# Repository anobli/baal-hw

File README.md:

# Beal

Beal is a **LoRa valve-control proxy** that retrofits an existing irrigation
controller with remote, wire-free zone control.

## Why

Irrigation controllers are typically wire-only: reaching a new zone, or a
valve far from the controller box, means trenching new low-voltage wiring
across a working field — labor-intensive and disruptive.

Beal solves that wiring problem: clip a **RX** unit onto the existing
controller (no new wiring, no controller replacement) and place **TX** units
directly at the valves; they talk over LoRa, so control reaches valves
without trenching.

## How it works

Two dedicated boards make up one system:

| Board | Role | What it does |
| --- | --- | --- |
| [**Beal-Rx**](Beal-Rx/README.md) | Input | Clips onto the existing controller's zone-output wiring, senses which zone it's energizing, and reports over LoRa. Acts as the LoRa coordinator. |
| [**Beal-TX**](Beal-TX/README.md) | Output | Lives out at the valves, powered by its own battery + solar supply. Drives valve solenoids on command from Beal-Rx. Acts as a LoRa peer. |

```mermaid
flowchart TD
    VC["Existing valve controller<br/>(zone outputs)"] -->|wired, no new cabling| RX["Beal-Rx<br/>LoRa coordinator"]
    RX -->|LoRa P2P, star topology| TX1["Beal-TX #1<br/>LoRa peer"]
    RX -->|LoRa P2P, star topology| TX2["Beal-TX #2<br/>LoRa peer"]
    TX1 -->|wired| V1["Valves — zone A"]
    TX2 -->|wired| V2["Valves — zone B"]
```

The link between Beal-Rx and Beal-TX units is point-to-point LoRa, not
LoRaWAN: a custom, open-source stack with a star topology. Beal-Rx is the
coordinator — it's where commands originate and it's already the central
device by virtue of being wired to the existing controller. Beal-TX units are
peer nodes that take commands from it. LoRaWAN is deliberately avoided for
now — it would require network-server infrastructure disproportionate to
stand up and operate for this product.

## Repository layout

| Folder | What it is |
| --- | --- |
| [`Beal-Rx/`](Beal-Rx/README.md) | Input board: KiCad project, schematics, PCB. |
| [`Beal-TX/`](Beal-TX/README.md) | Output board: KiCad project, schematics, PCB. |
| `Beal-Common/` | Reusable elements shared between boards — currently footprints, with symbol libraries and design blocks planned. |

Schematic PDFs and BOMs are generated automatically on every push via
[`.github/workflows/kicad-schematic-pdf.yml`](.github/workflows/kicad-schematic-pdf.yml).

## What's next: Beal Controller

Both boards share the same LoRa-E5-centric approach, which is also the seed
for a future third board — tentatively **Beal Controller**. It would be a
smart irrigation controller with its own valve outputs and smart features
(weather-driven scheduling, ET0 computation, local web UI), while still able
to control remote valves over LoRa through a Beal-TX unit — replacing the
third-party controller entirely instead of just retrofitting it. This is a
future direction, not yet designed.

## License

Hardware design files are licensed under the
[CERN Open Hardware Licence Version 2 - Strongly Reciprocal](LICENSE).

## Open items

- [ ] Battery chemistry/capacity for the Beal-TX power pack — not yet sized.
- [ ] Enclosure — to do, no design started.
- [ ] Regulatory/certification path for the radio — not started; complicated
      by the use of a custom (non-LoRaWAN) PHY/MAC stack.
- [ ] Unit cost target (below 250 € incl. VAT) — needs re-costing against the
      current RX/TX design.
- [ ] Beal Controller — not designed yet; see above.

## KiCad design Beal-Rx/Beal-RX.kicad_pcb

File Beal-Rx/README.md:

# Beal-Rx — input board

Beal-Rx clips onto an existing irrigation controller's zone-output wiring,
senses which zone it's energizing, and reports that over LoRa to one or more
[Beal-TX](../Beal-TX/README.md) units. It is the LoRa coordinator of a Beal
system — it's where commands originate, and it's already the natural central
device since it's the one wired to the existing controller.

The schematic is split into three sheets: **Inputs**, **Radio**, **Power**.

## Inputs (`io_ext.kicad_sch`)

- 12 sense channels, each isolated from the field wiring by an opto-isolator
  (3× LTV-844S, 4 channels each). This gives galvanic isolation from whatever
  the existing controller puts on its zone outputs, with no current drawn
  from or injected back into the controller.
- Sized against 24VAC zone outputs but tolerant of smaller signals
  (9VAC/9VDC), so the same board can read other controller types without a
  hardware change.
- A 14-position terminal block (`TBL004-508-14BE-2GY`) brings in the 12
  channels plus the shared `INPUT_COM` return.
- A dedicated **STM32C031K6Ux MCU** on this sheet scans all 12 opto outputs
  and reports state changes up to the LoRa-E5 (I2C/UART, plus an interrupt
  line) — the LoRa-E5 doesn't have enough spare GPIOs to read 12 channels
  directly itself, so this small companion MCU owns the input-scanning job.
  It has its own SWD (TC2050) connector for programming/debug.

## Radio (`radio_mcu.kicad_sch`)

- **LoRa-E5 module** (U5, Seeed, STM32WL-based) — the application MCU. It
  owns the LoRa radio, drives the status LED (D3), reads the pairing button
  (SW2, on its own dedicated GPIO), and talks to the Inputs sheet's
  STM32C031 over I2C/UART to learn which zone just turned on.
- Pairing button (SW2) behavior:
  - Short press: pairs this coordinator with a Beal-TX peer (implemented).
  - Double press: maps a specific input channel to a specific output channel
    on a specific Beal-TX (planned, procedure still TBD).
  - Long press: probable factory reset (not decided).
- U.FL/antenna connector (J1) for the 868 MHz antenna.
- USB-C connector (J5) — power input only.
- SWD (Tag-Connect J7) for programming/debugging the LoRa-E5.
- One extension connector (J2, `Conn_02x04_Odd_Even`) reserved for a future
  add-on board (e.g. more sense inputs) — not used by anything today.

## Power (`power.kicad_sch`)

- `TPSM863253` buck power module producing the board's logic-level rail from
  USB 5V. No boost converter or valve driver on this board — Beal-Rx only
  senses, it never drives anything, so it has no need for the 9V drive rail
  that Beal-TX needs.
- Powered from a 5V USB supply (mains-adapter or similar) — it lives next to
  the existing controller, which typically has power available nearby.

## Open items

- [ ] Channel-to-channel mapping procedure (input on Beal-Rx → output on a
      specific Beal-TX) — design not finalized.
- [ ] Long-press button behavior (factory reset) — not decided.
- [ ] Extension connector (J2) use case — reserved, nothing designed against
      it yet.

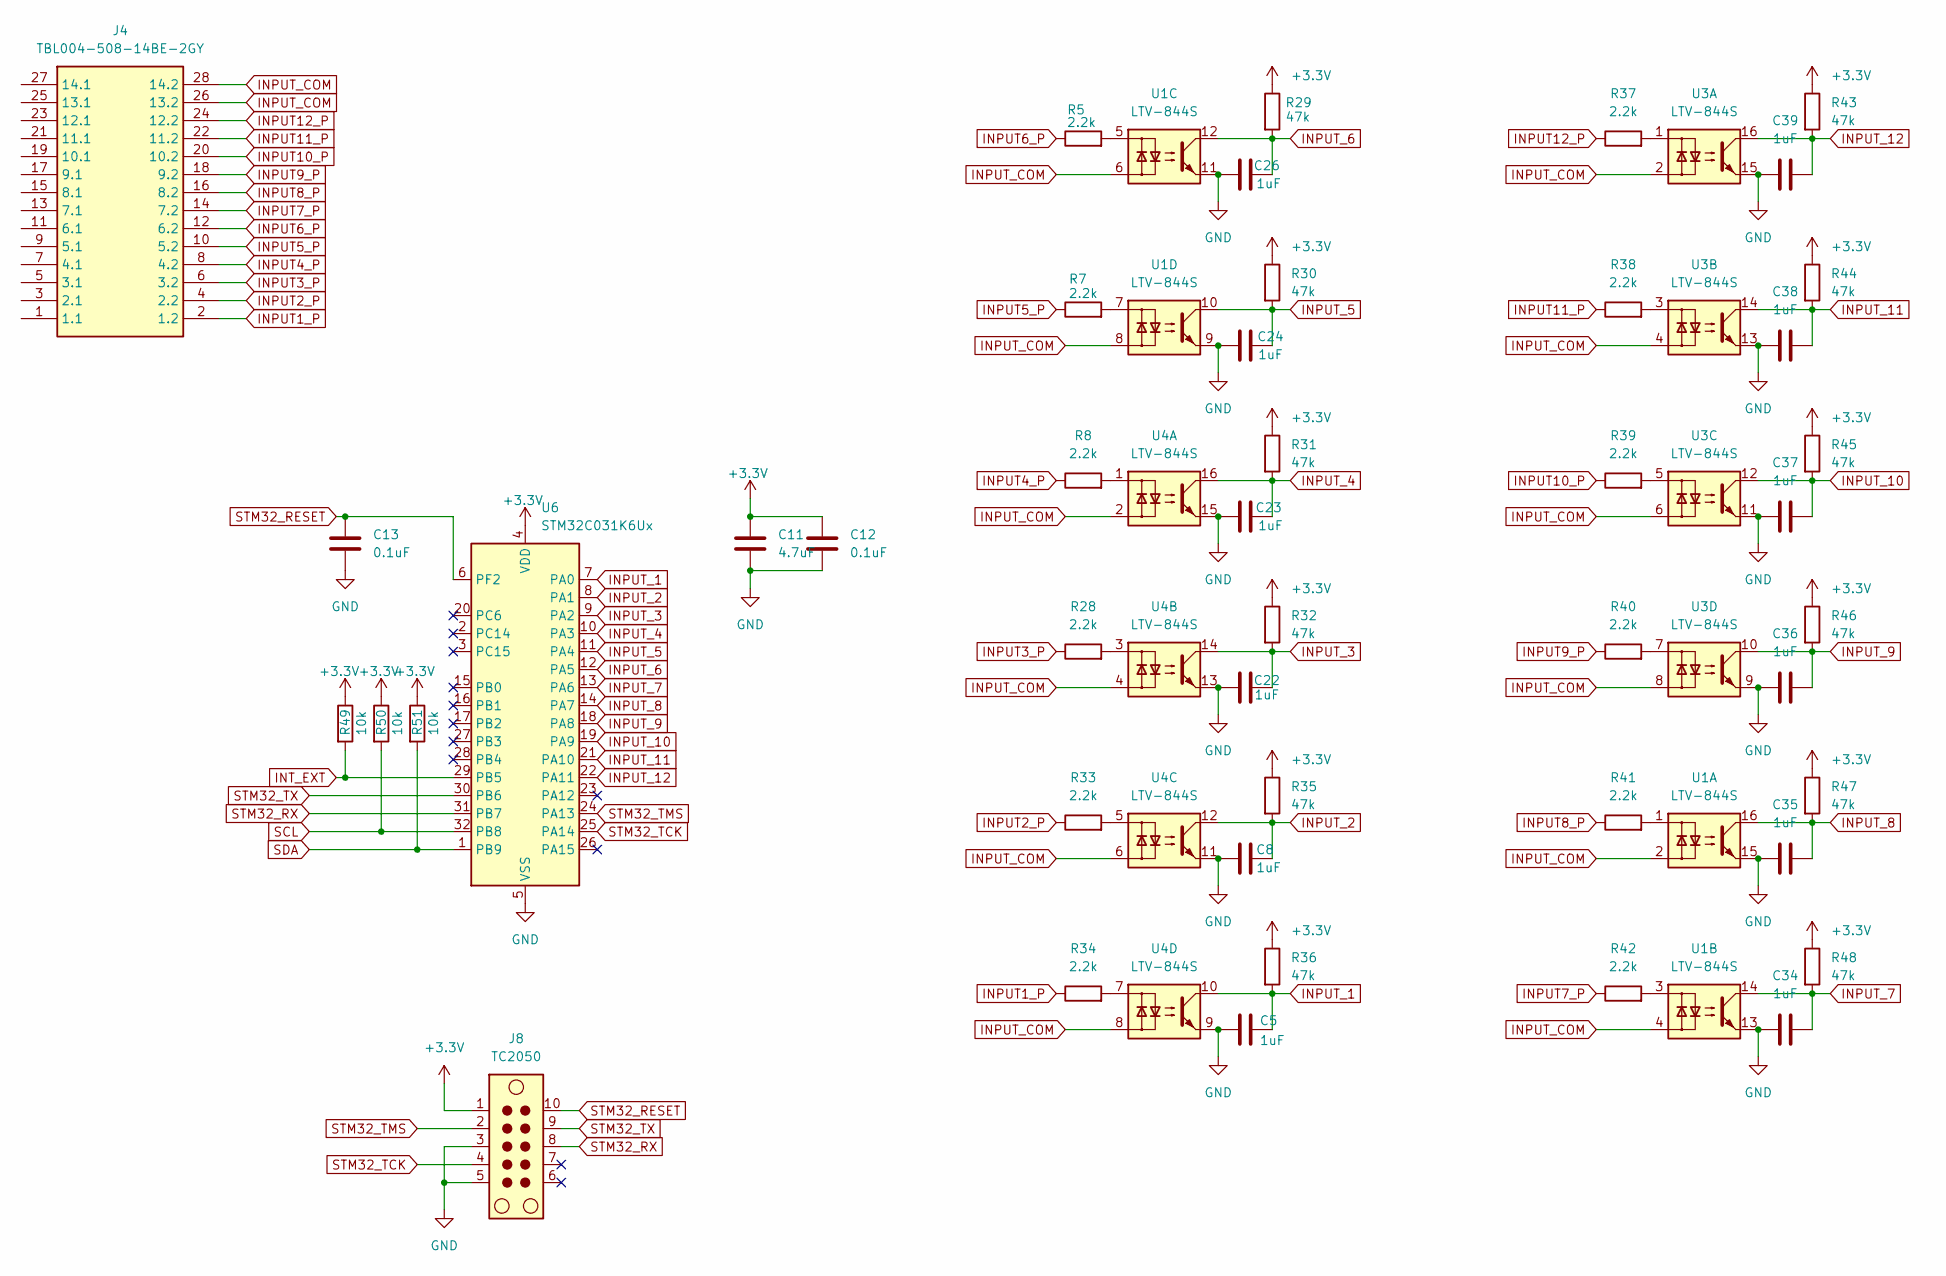
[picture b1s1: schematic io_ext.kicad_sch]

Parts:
C5, C8, C22, C23, C24, C26, C34, C35, C36, C37, C38, C39: 1uF; C_0603_1608Metric; Manufacturer_Part_Number 1uF 16V 0603
C11: 4.7uF; C_0805_2012Metric; MPN 4.7uF 10V 0805
C12, C13: 0.1uF; C_0805_2012Metric; MPN 0.1uF 10V 0805
J4: TBL004-508-14BE-2GY; Mouser Part Number 490-TBL00450814BE2GY
J8: TC2050; Tag-Connect_TC2050-IDC-NL_2x05_P1.27mm_Vertical
R5, R7, R8, R28, R33, R34, R37, R38, R39, R40, R41, R42: 2.2k; R_0402_1005Metric; Manufacturer_Part_Number 2.2K 0402
R29, R30, R31, R32, R35, R36, R43, R44, R45, R46, R47, R48: 47k; R_0402_1005Metric; Manufacturer_Part_Number 47K 0402
R49, R50, R51: 10k; R_0402_1005Metric; MPN 10k 0402
U1, U3, U4: LTV-844S; SMDIP-16_W9.53mm; MPN LTV-844S
U6: STM32C031K6Ux; QFN-32-1EP_5x5mm_P0.5mm_EP3.45x3.45mm; MPN STM32C031K6U6

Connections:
+3.3V: C11.1, C12.1, J8.1, R29.1, R30.1, R31.1, R32.1, R35.1, R36.1, R43.1, R44.1, R45.1, R46.1, R47.1, R48.1, R49.1, R50.1, R51.1, U6.4 (VDD); also elsewhere on the board
GND: C5.1, C8.2, C11.2, C12.2, C13.2, C22.1, C23.1, C24.2, C26.2, C34.1, C35.1, C36.1, C37.1, C38.2, C39.1, J8.3, J8.5, U1.9, U1.11, U1.13, U1.15, U3.9, U3.11, U3.13, U3.15, U4.9, U4.11, U4.13, U4.15, U6.5 (VSS), U6.33 (VSS); also elsewhere on the board
INPUT1_P: J4.2 (1.2), R34.1
INPUT2_P: J4.4 (2.2), R33.1
INPUT3_P: J4.6 (3.2), R28.1
INPUT4_P: J4.8 (4.2), R8.1
INPUT5_P: J4.10 (5.2), R7.1
INPUT6_P: J4.12 (6.2), R5.1
INPUT7_P: J4.14 (7.2), R42.1
INPUT8_P: J4.16 (8.2), R41.1
INPUT9_P: J4.18 (9.2), R40.1
INPUT10_P: J4.20 (10.2), R39.1
INPUT11_P: J4.22 (11.2), R38.1
INPUT12_P: J4.24 (12.2), R37.1
INPUT_1: C5.2, R36.2, U4.10, U6.7 (PA0)
INPUT_2: C8.1, R35.2, U4.12, U6.8 (PA1)
INPUT_3: C22.2, R32.2, U4.14, U6.9 (PA2)
INPUT_4: C23.2, R31.2, U4.16, U6.10 (PA3)
INPUT_5: C24.1, R30.2, U1.10, U6.11 (PA4)
INPUT_6: C26.1, R29.2, U1.12, U6.12 (PA5)
INPUT_7: C34.2, R48.2, U1.14, U6.13 (PA6)
INPUT_8: C35.2, R47.2, U1.16, U6.14 (PA7)
INPUT_9: C36.2, R46.2, U3.10, U6.18 (PA8)
INPUT_10: C37.2, R45.2, U3.12, U6.19 (PA9)
INPUT_11: C38.1, R44.2, U3.14, U6.21 (PA10)
INPUT_12: C39.2, R43.2, U3.16, U6.22 (PA11)
INPUT_COM: J4.26 (13.2), J4.28 (14.2), U1.2, U1.4, U1.6, U1.8, U3.2, U3.4, U3.6, U3.8, U4.2, U4.4, U4.6, U4.8
INT_EXT: R49.2, U6.29 (PB5); also elsewhere on the board
unnamed: R5.2, U1.5
unnamed: R7.2, U1.7
unnamed: R8.2, U4.1
unnamed: R28.2, U4.3
unnamed: R33.2, U4.5
unnamed: R34.2, U4.7
unnamed: R37.2, U3.1
unnamed: R38.2, U3.3
unnamed: R39.2, U3.5
unnamed: R40.2, U3.7
unnamed: R41.2, U1.1
unnamed: R42.2, U1.3
SCL: R50.2, U6.32 (PB8); also elsewhere on the board
SDA: R51.2, U6.1 (PB9); also elsewhere on the board
STM32_RESET: C13.1, J8.10, U6.6 (PF2)
STM32_RX: J8.8, U6.31 (PB7)
STM32_TCK: J8.4, U6.25 (PA14)
STM32_TMS: J8.2, U6.24 (PA13)
STM32_TX: J8.9, U6.30 (PB6)

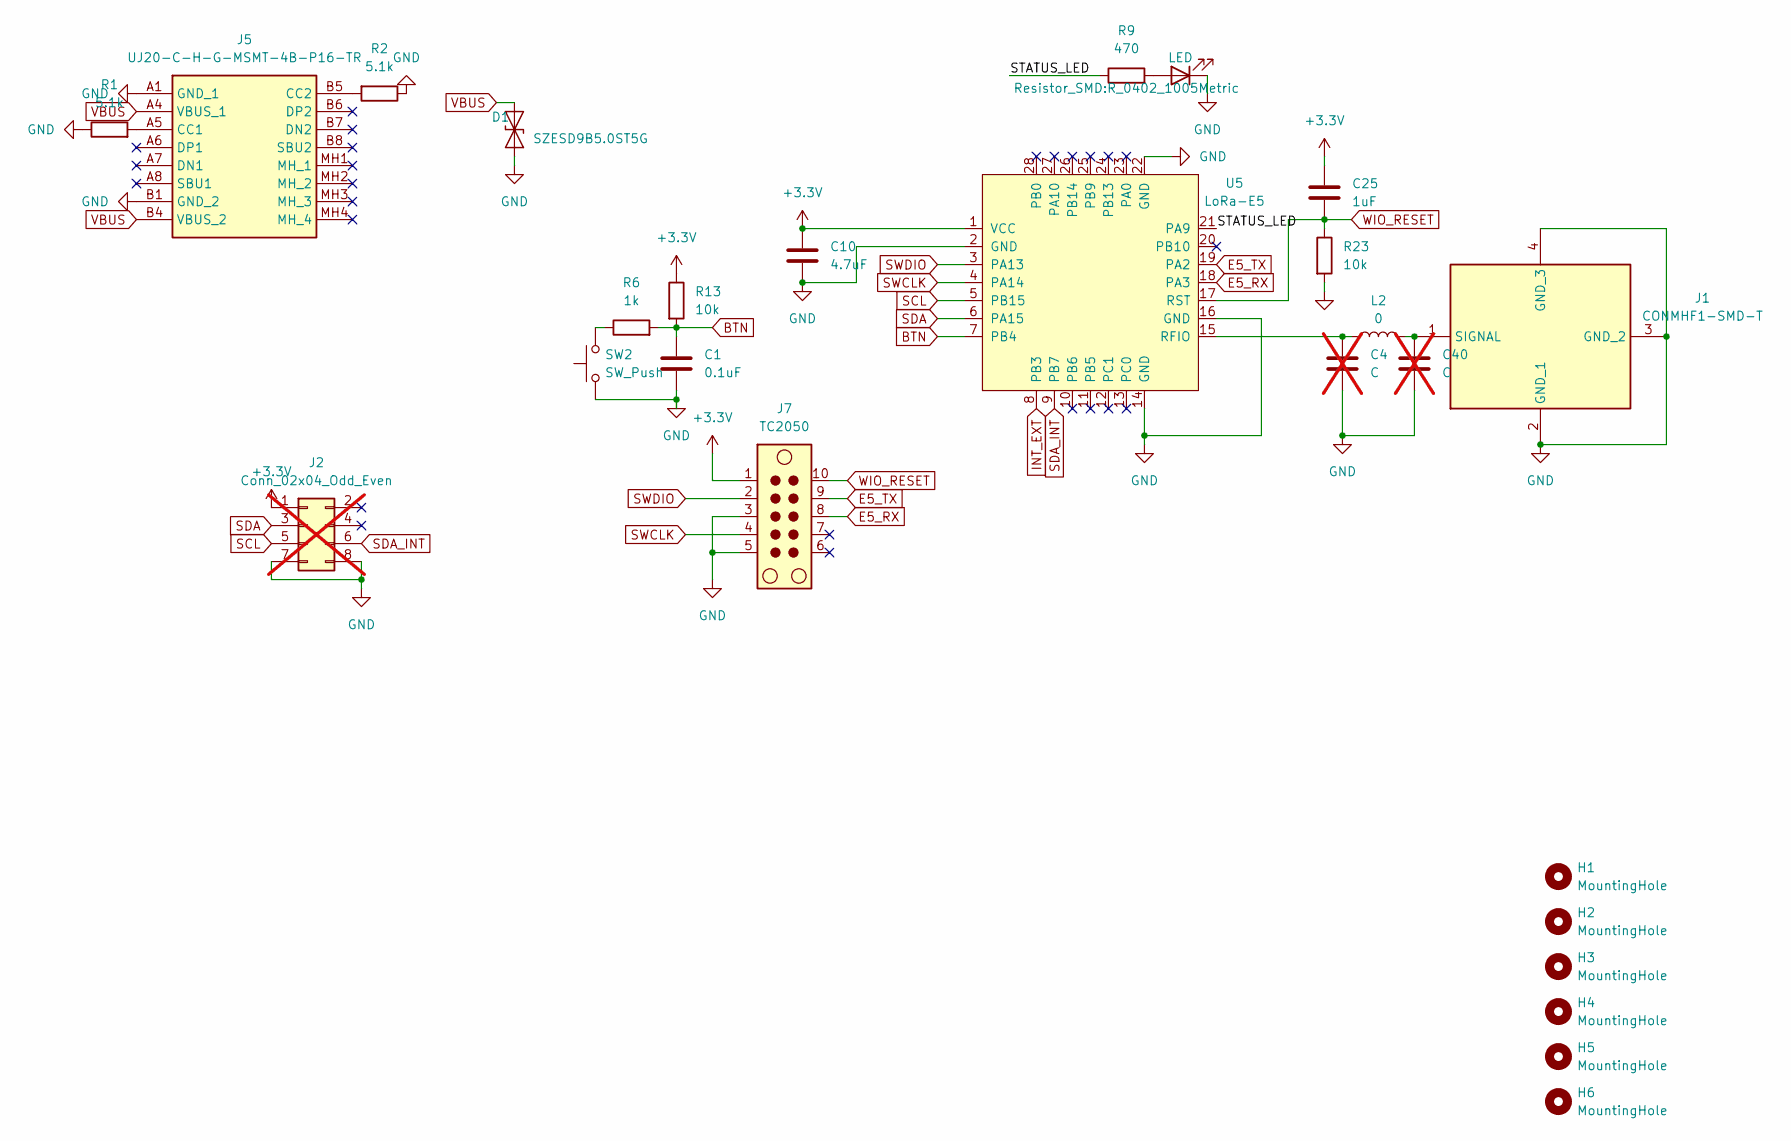
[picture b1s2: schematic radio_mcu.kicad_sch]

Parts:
C1: 0.1uF; C_0805_2012Metric; MPN 0.1uF 16V 0805
C4, C40: C; C_0603_1608Metric; not fitted
C10: 4.7uF; C_0805_2012Metric; MPN 4.7uF 10V 0805
C25: 1uF; C_0603_1608Metric; Manufacturer_Part_Number 1uF 16V 0603
D1: SZESD9B5.0ST5G; D_SOD-923; MPN SZESD9B5.0ST5G
D3: LED; LED_0603_1608Metric; Manufacturer_Part_Number led red 1206
H1, H2, H3, H4, H5, H6: MountingHole; MountingHole_2.1mm
J1: CONMHF1-SMD-T; CONMHF1SMDT; Mouser Part Number 712-CONMHF1-SMD-T
J2: Conn_02x04_Odd_Even; PinHeader_2x04_P1.00mm_Vertical_SMD; not fitted
J5: UJ20-C-H-G-MSMT-4B-P16-TR; UJ20CHGMSMT4BP16TR; Manufacturer_Part_Number UJ20-C-H-G-MSMT-4B-P16-TR
J7: TC2050; Tag-Connect_TC2050-IDC-NL_2x05_P1.27mm_Vertical
L2: 0; L_0603_1608Metric; Manufacturer_Part_Number 0K 0603
R1, R2: 5.1k; R_0402_1005Metric; Manufacturer_Part_Number 5.1K 0402
R6: 1k; R_0402_1005Metric; MPN 1K 0402
R9: 470; R_0402_1005Metric; MPN 470 0402
R13: 10k; R_0402_1005Metric; MPN 10K 0402
R23: 10k; R_0402_1005Metric; Manufacturer_Part_Number 10K 0402
SW2: SW_Push; SW_Tactile_SPST_Angled_PTS645Vx83-2LFS
U5: LoRa-E5; MPN LORA-E5 LORAWAN MODULE

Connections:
+3.3V: C10.1, C25.1, J2.1, J7.1, R13.1, U5.1 (VCC); also elsewhere on the board
/Radio/STATUS_LED: R9.1, U5.21 (PA9)
BTN: C1.1, R6.2, R13.2, U5.7 (PB4)
E5_RX: J7.8, U5.18 (PA3)
E5_TX: J7.9, U5.19 (PA2)
GND: C1.2, C4.2, C10.2, C40.2, D1.1 (A1), D3.1 (K), J1.2 (GND_1), J1.3 (GND_2), J1.4 (GND_3), J2.7, J2.8, J5.A1 (GND_1), J5.B1 (GND_2), J7.3, J7.5, R1.1, R2.1, R23.2, SW2.1, U5.2 (GND), U5.14 (GND), U5.16 (GND), U5.22 (GND); also elsewhere on the board
INT_EXT: U5.8 (PB3); also elsewhere on the board
unnamed: D3.2 (A), R9.2
unnamed: C40.1, J1.1 (SIGNAL), L2.2
unnamed: J5.A5 (CC1), R1.2
unnamed: J5.B5 (CC2), R2.2
unnamed: R6.1, SW2.2
unnamed: C4.1, L2.1, U5.15 (RFIO)
SCL: J2.5, U5.5 (PB15); also elsewhere on the board
SDA: J2.3, U5.6 (PA15); also elsewhere on the board
SDA_INT: J2.6, U5.9 (PB7)
SWCLK: J7.4, U5.4 (PA14)
SWDIO: J7.2, U5.3 (PA13)
VBUS: D1.2 (A2), J5.A4 (VBUS_1), J5.B4 (VBUS_2); also elsewhere on the board
WIO_RESET: C25.2, J7.10, R23.1, U5.17 (RST)

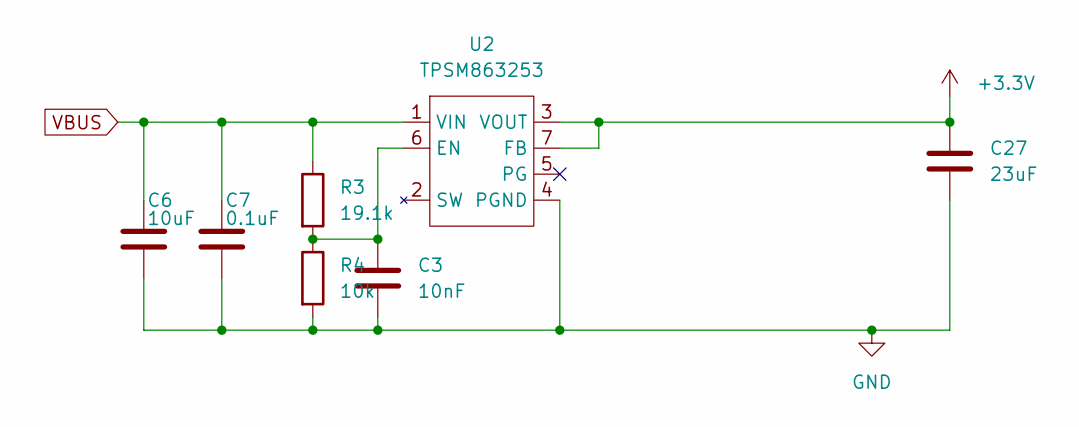
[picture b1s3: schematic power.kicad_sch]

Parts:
C3: 10nF; C_0402_1005Metric; Manufacturer_Part_Number GRM155R71C103KA01D
C6: 10uF; C_0805_2012Metric; Manufacturer_Part_Number C0805C106K8PACTU
C7: 0.1uF; C_0805_2012Metric; Manufacturer_Part_Number 08053C104KAT2A
C27: 23uF; C_0805_2012Metric; Manufacturer_Part_Number MSASL219LB5226MTNA01
R3: 19.1k; R_0402_1005Metric; Manufacturer_Part_Number CRCW040219K1FKED
R4: 10k; R_0402_1005Metric; Manufacturer_Part_Number CRCW040210K0FKED
U2: TPSM863253; Texas_RDX0007A_QFN-FCMOD-7-3.3x4mm-P0.5mm_4EP; MPN TPSM863253RDXR

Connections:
+3.3V: C27.1, U2.3 (VOUT), U2.7 (FB); also elsewhere on the board
GND: C3.2, C6.2, C7.2, C27.2, R4.2, U2.4 (PGND); also elsewhere on the board
unnamed: C3.1, R3.2, R4.1, U2.6 (EN)
VBUS: C6.1, C7.1, R3.1, U2.1 (VIN); also elsewhere on the board

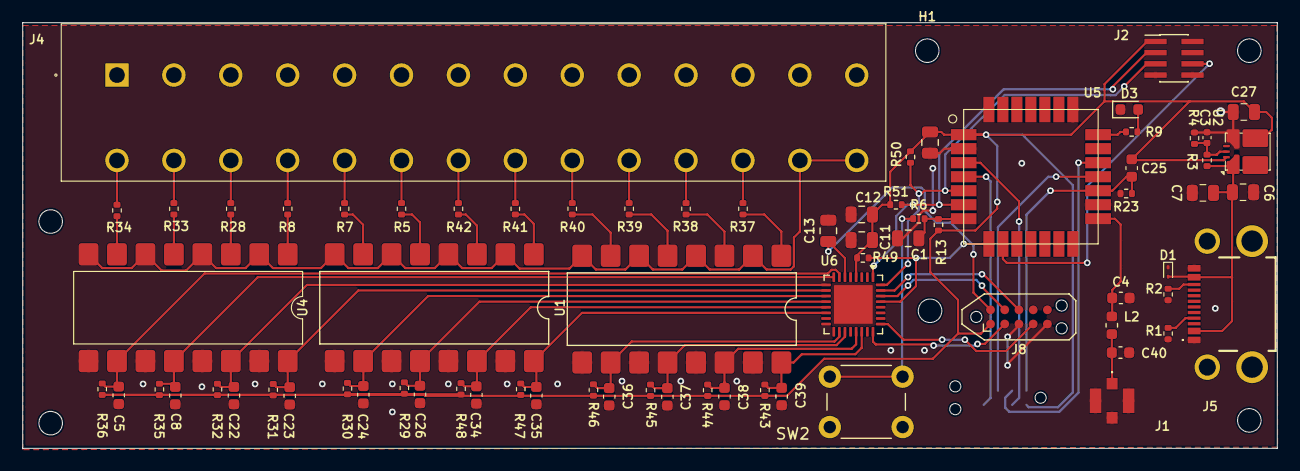
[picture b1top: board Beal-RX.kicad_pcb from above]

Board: 2 copper layers, 112.0 x 38.0 mm, 81 parts (1 on the bottom side), 63 nets.

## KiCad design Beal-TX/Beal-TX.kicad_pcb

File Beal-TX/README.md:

# Beal-TX — output board

Beal-TX lives out in the field at the valves, powered by its own battery +
solar supply. It receives commands over LoRa from a [Beal-Rx](../Beal-Rx/README.md)
unit and drives valve solenoids accordingly. It is a LoRa peer node — it has
no wired connection to the existing controller, and only acts on commands
sent by the coordinator.

The schematic is split into three sheets: **I/O Ext Board Output**
(`input.kicad_sch` — the sheet name is more accurate than the filename,
which is a naming leftover), **Radio_MCU**, **Power**.

## I/O Ext Board Output (`input.kicad_sch`)

- **DRV8912QPWPRQ1** (U6) — a 12-channel automotive smart driver, controlled
  directly by the LoRa-E5 over SPI (`SDI`/`SDO`/`SCLK`/`SCS_N`), with
  `SLEEP_N`/`FAULT_N` handshake lines. There is no companion MCU on this
  board — unlike Beal-Rx's Inputs sheet, the LoRa-E5 talks to the driver
  itself.
- 3 valve output channels (`OUTPUT1`–`OUTPUT3`), each driven as a full
  H-bridge — not a shared-common topology. Each DRV8912 half-bridge is
  limited to 1A RMS, which isn't enough for the target valves, so each side
  of a valve's H-bridge is actually two DRV8912 half-bridges wired in
  parallel for extra current headroom. That's 4 half-bridges per valve
  (2 for the P side, 2 for the N side), which is why the driver's 12
  channels only yield 3 valve outputs rather than 6. Target valves are 9VDC
  latching solenoids (a latching valve needs only a brief pulse of the
  correct polarity to switch, then holds its position with no power
  applied — a good fit for a battery/solar-powered field unit).
- 3 status LEDs (`LED1`–`LED3`), one per valve channel.
- Field wiring lands on a 6-position screw terminal (J6, `691401710006B`) —
  6 pins for the 3 valve channels' P/N pairs.
- Fault detection matters more here than in a typical hobby project: a
  stuck-open or undetected-failed valve can waste water or damage a crop.
  Careful use of the DRV8912's `FAULT_N` reporting is a design requirement,
  not a nice-to-have.

## Radio_MCU (`radio_mcu.kicad_sch`)

- **LoRa-E5 module** (U5, Seeed, STM32WL-based) — the application MCU. It
  owns the LoRa radio, drives the status LED, reads the pairing button, and
  drives the DRV8912 directly over SPI.
- Pairing button behavior mirrors Beal-Rx:
  - Short press: pairs this peer with a Beal-Rx coordinator (implemented).
  - Double press: maps a specific output channel to a specific input channel
    on the paired Beal-Rx (planned, procedure still TBD).
  - Long press: probable factory reset (not decided).
- U.FL/antenna connector for the 868 MHz antenna.
- SWD (Tag-Connect) for programming/debugging the LoRa-E5.
- Two extension connectors (`Conn_02x04_Odd_Even`) reserved for future
  add-on boards — not used by anything today. Planned (not yet designed)
  candidates:
  - a sensor input module (flow meter, humidity sensor);
  - a second MCU board with an ESP32, adding smart features and WiFi/BT
    connectivity;
  - possibly an output-expansion board, to drive more than 3 valves from one
    Beal-TX.

## Power (`power.kicad_sch`)

- `TPSM863253` buck power module for the board's logic-level rail.
- `LM5157-Q1` (gated by `9V_EN`) boosts up to 9V to feed the DRV8912 — the
  drive voltage the target latching solenoid valves need for a latch pulse.
- Powered from a battery + solar pack, delivered to the board as 5V over the
  same USB-C connector type used on Beal-Rx (the board only sees a `VBUS`
  net — battery/solar sourcing happens in the external power pack).
- Automotive-grade parts are used deliberately, not for automotive
  compliance but because the board sits in an outdoor enclosure that can see
  high internal temperatures from direct sun exposure — automotive parts
  give margin on temperature rating (and generally ESD/robustness) that
  consumer-grade parts don't.

## Open items

- [ ] Channel-to-channel mapping procedure — design not finalized (shared
      with Beal-Rx, see its README).
- [ ] Long-press button behavior (factory reset) — not decided.
- [ ] Both extension connectors — reserved for planned add-on boards
      (sensor input module, ESP32 MCU board, output-expansion board), none
      designed yet.
- [ ] Battery chemistry/capacity for the power pack — not yet sized.

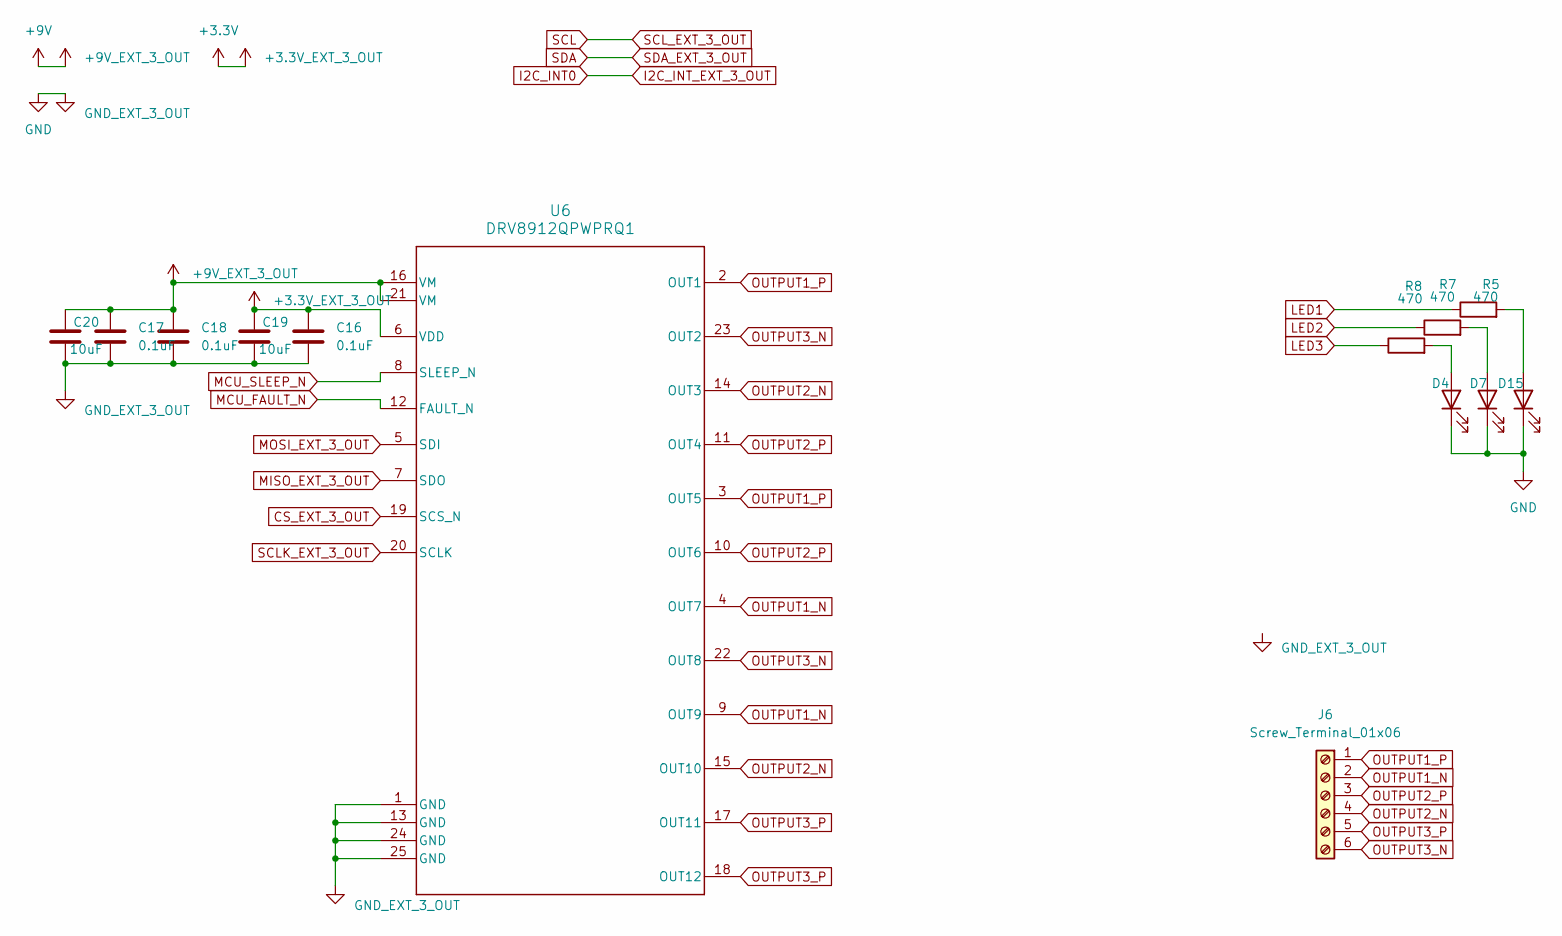
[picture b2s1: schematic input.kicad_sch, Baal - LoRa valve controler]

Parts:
C16: 0.1uF; C_0402_1005Metric; Manufacturer_Part_Number 0,1uF 16V 0402
C17, C18: 0.1uF; C_0805_2012Metric; Manufacturer_Part_Number 0,1uF 50V 0805
C19: 10uF; C_0805_2012Metric; MPN 10uF 10V 0805
C20: 10uF; R_1206_3216Metric; MPN GRM31CR71C106KAC7L
D4, D7, D15: LED; LED_0603_1608Metric; Manufacturer_Part_Number led red 1206
J6: Screw_Terminal_01x06; 691401710006B; MPN 691401710006B
R5: 470; R_0402_1005Metric
R7, R8: 470; R_0402_1005Metric; MPN 470 0402
U6: DRV8912QPWPRQ1; HTSSOP-24-1EP_4.4x7.8mm_P0.65mm_EP3.4x7.8mm_Mask2.4x4.68mm_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; Manufacturer_Part_Number DRV8912QPWPRQ1

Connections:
+3.3V: C16.1, C19.1, U6.6 (VDD); also elsewhere on the board
+9V: C17.1, C18.1, C20.1, U6.16 (VM), U6.21 (VM); also elsewhere on the board
CS_EXT_3_OUT: U6.19 (SCS_N); also elsewhere on the board
GND: C16.2, C17.2, C18.2, C19.2, C20.2, D4.1 (K), D7.1 (K), D15.1 (K), U6.1 (GND), U6.13 (GND), U6.24 (GND), U6.25 (GND); also elsewhere on the board
LED1: R5.1; also elsewhere on the board
LED2: R7.1; also elsewhere on the board
LED3: R8.1; also elsewhere on the board
MCU_FAULT_N: U6.12 (FAULT_N); also elsewhere on the board
MCU_SLEEP_N: U6.8 (SLEEP_N); also elsewhere on the board
MISO_EXT_3_OUT: U6.7 (SDO); also elsewhere on the board
MOSI_EXT_3_OUT: U6.5 (SDI); also elsewhere on the board
unnamed: D4.2 (A), R8.2
unnamed: D7.2 (A), R7.2
unnamed: D15.2 (A), R5.2
OUTPUT1_N: J6.2, U6.4 (OUT7), U6.9 (OUT9)
OUTPUT1_P: J6.1, U6.2 (OUT1), U6.3 (OUT5)
OUTPUT2_N: J6.4, U6.14 (OUT3), U6.15 (OUT10)
OUTPUT2_P: J6.3, U6.10 (OUT6), U6.11 (OUT4)
OUTPUT3_N: J6.6, U6.22 (OUT8), U6.23 (OUT2)
OUTPUT3_P: J6.5, U6.17 (OUT11), U6.18 (OUT12)
SCLK_EXT_3_OUT: U6.20 (SCLK); also elsewhere on the board

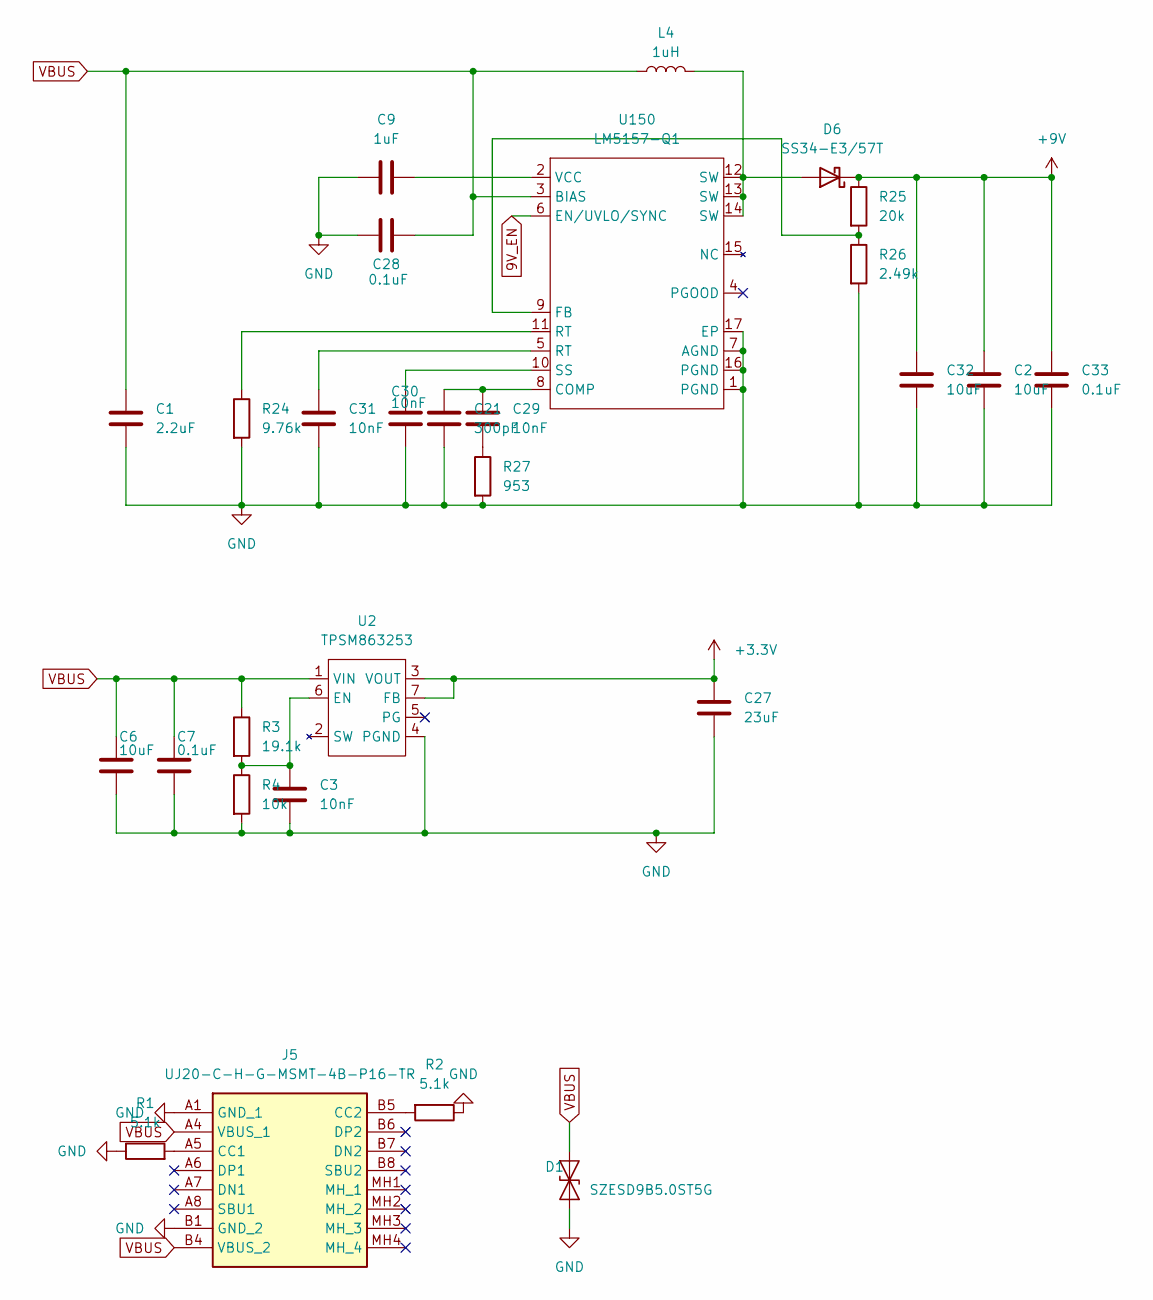
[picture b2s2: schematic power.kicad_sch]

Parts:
C1: 2.2uF; C_0805_2012Metric; Manufacturer_Part_Number GRM21BR71A225KA01L
C2, C32: 10uF; C_1206_3216Metric; Manufacturer_Part_Number GRM31CR71C106KAC7L
C3: 10nF; C_0402_1005Metric; Manufacturer_Part_Number GRM155R71C103KA01D
C6: 10uF; C_0805_2012Metric; Manufacturer_Part_Number C0805C106K8PACTU
C7: 0.1uF; C_0805_2012Metric; Manufacturer_Part_Number 08053C104KAT2A
C9: 1uF; C_0603_1608Metric; Manufacturer_Part_Number EMK107B7105KA-T
C21: 300pF; C_0402_1005Metric; Manufacturer_Part_Number GRM1555C1E301JA01D
C27: 23uF; C_0805_2012Metric; Manufacturer_Part_Number MSASL219LB5226MTNA01
C28: 0.1uF; C_0402_1005Metric; Manufacturer_Part_Number GRM155R71A104KA01D
C29, C30, C31: 10nF; C_0402_1005Metric; Manufacturer_Part_Number GRM155R70J103KA01D
C33: 0.1uF; C_0805_2012Metric; Manufacturer_Part_Number GRM155R71C104KA88D
D1: SZESD9B5.0ST5G; D_SOD-923; MPN SZESD9B5.0ST5G
D6: SS34-E3/57T; D_SMB; Manufacturer_Part_Number SS34-E3/57T
J5: UJ20-C-H-G-MSMT-4B-P16-TR; UJ20CHGMSMT4BP16TR; Manufacturer_Part_Number UJ20-C-H-G-MSMT-4B-P16-TR
L4: 1uH; L_Wuerth_WE-PD-Typ-7345; Manufacturer_Part_Number 744777001
R1, R2: 5.1k; R_0402_1005Metric; Manufacturer_Part_Number 5.1K 0402
R3: 19.1k; R_0402_1005Metric; Manufacturer_Part_Number CRCW040219K1FKED
R4: 10k; R_0402_1005Metric; Manufacturer_Part_Number CRCW040210K0FKED
R24: 9.76k; R_0402_1005Metric; Manufacturer_Part_Number CRCW04029K76FKED
R25: 20k; R_0402_1005Metric; Manufacturer_Part_Number CRCW040220K0FKED
R26: 2.49k; R_0402_1005Metric; Manufacturer_Part_Number CRCW04022K49FKED
R27: 953; R_0402_1005Metric; Manufacturer_Part_Number CRCW0402953RFKED
U2: TPSM863253; Texas_RDX0007A_QFN-FCMOD-7-3.3x4mm-P0.5mm_4EP; MPN TPSM863253RDXR
U150: LM5157-Q1; WQFN-16-1EP_3x3mm_P0.5mm_EP1.68x1.68mm_ThermalVias; Manufacturer_Part_Number LM5157QRTERQ1

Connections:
9V_EN: U150.6 (EN/UVLO/SYNC); also elsewhere on the board
+3.3V: C27.1, U2.3 (VOUT), U2.7 (FB); also elsewhere on the board
+9V: C2.1, C32.1, C33.1, D6.1 (K), R25.1; also elsewhere on the board
GND: C1.2, C2.2, C3.2, C6.2, C7.2, C9.2, C21.2, C27.2, C28.1, C30.2, C31.2, C32.2, C33.2, D1.1 (A1), J5.A1 (GND_1), J5.B1 (GND_2), R1.1, R2.1, R4.2, R24.2, R26.2, R27.2, U2.4 (PGND), U150.1 (PGND), U150.7 (AGND), U150.16 (PGND), U150.17 (EP); also elsewhere on the board
unnamed: C29.2, R27.1
unnamed: C31.1, U150.5 (RT)
unnamed: D6.2 (A), L4.2, U150.12 (SW), U150.13 (SW), U150.14 (SW)
unnamed: J5.A5 (CC1), R1.2
unnamed: J5.B5 (CC2), R2.2
unnamed: R24.1, U150.11 (RT)
unnamed: C3.1, R3.2, R4.1, U2.6 (EN)
unnamed: C21.1, C29.1, U150.8 (COMP)
unnamed: R25.2, R26.1, U150.9 (FB)
unnamed: C30.1, U150.10 (SS)
unnamed: C9.1, U150.2 (VCC)
VBUS: C1.1, C6.1, C7.1, C28.2, D1.2 (A2), J5.A4 (VBUS_1), J5.B4 (VBUS_2), L4.1, R3.1, U2.1 (VIN), U150.3 (BIAS)

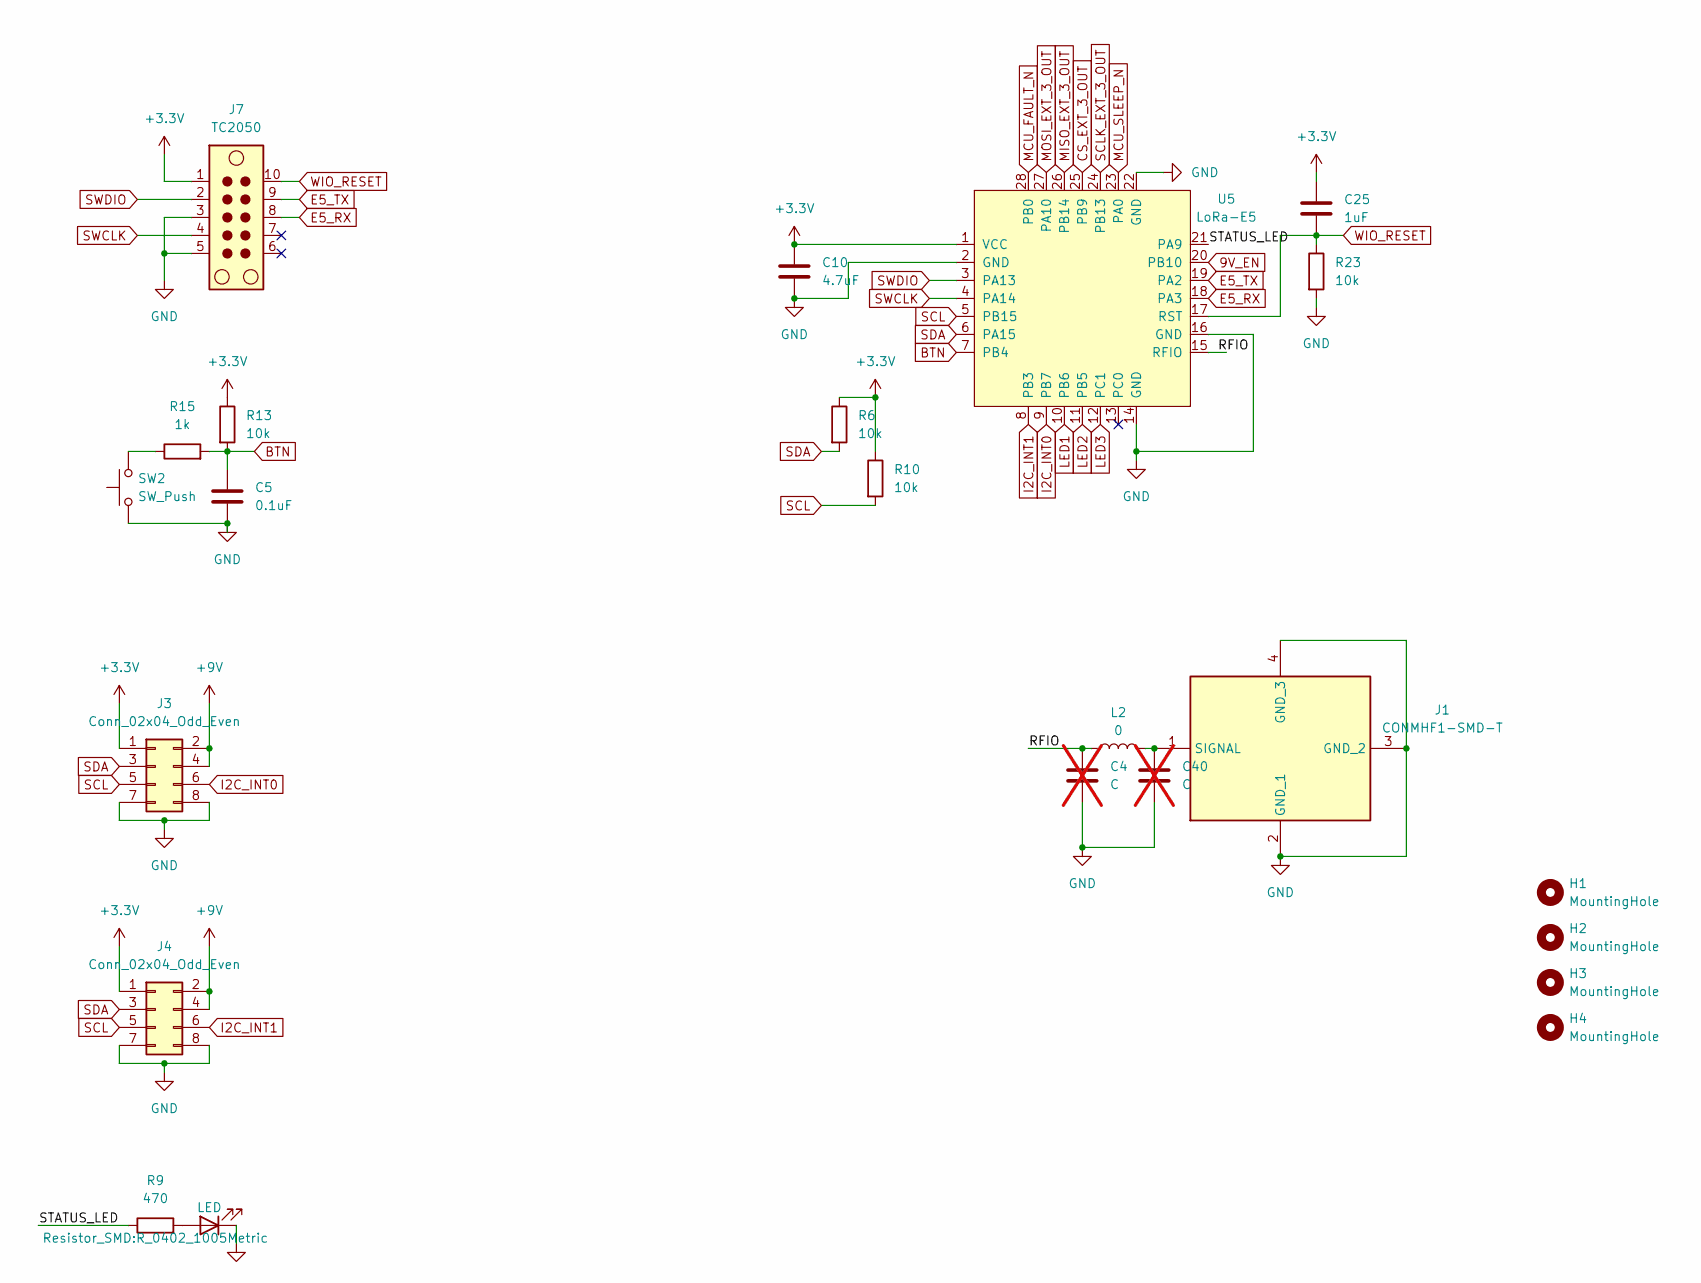
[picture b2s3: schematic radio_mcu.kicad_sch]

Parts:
C4, C40: C; C_0603_1608Metric; not fitted
C5: 0.1uF; C_0805_2012Metric; MPN 10uF 16V 0805
C10: 4.7uF; C_0805_2012Metric; MPN 4.7uF 10V 0805
C25: 1uF; C_0603_1608Metric; Manufacturer_Part_Number 1uF 16V 0603
D3: LED; LED_0603_1608Metric; Manufacturer_Part_Number led red 1206
H1, H2, H3, H4: MountingHole; MountingHole_2.1mm
J1: CONMHF1-SMD-T; CONMHF1SMDT; Mouser Part Number 712-CONMHF1-SMD-T
J3, J4: Conn_02x04_Odd_Even; PinHeader_2x04_P1.00mm_Vertical_SMD
J7: TC2050; Tag-Connect_TC2050-IDC-NL_2x05_P1.27mm_Vertical
L2: 0; L_0603_1608Metric; MPN RC0603FR-100RL
R6, R10: 10k; R_0402_1005Metric; MPN 10k 0402
R9: 470; R_0402_1005Metric; MPN 470 0402
R13: 10k; R_0402_1005Metric; MPN 10K 0402
R15: 1k; R_0402_1005Metric; MPN 1k 0402
R23: 10k; R_0402_1005Metric; Manufacturer_Part_Number 10K 0402
SW2: SW_Push; SW_PUSH_6mm; MPN TS02-66-43-BK-160-LCR-D
U5: LoRa-E5; MPN LORA-E5 LORAWAN MODULE

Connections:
9V_EN: U5.20 (PB10); also elsewhere on the board
+3.3V: C10.1, C25.1, J3.1, J4.1, J7.1, R6.1, R10.1, R13.1, U5.1 (VCC); also elsewhere on the board
+9V: J3.2, J3.4, J4.2, J4.4; also elsewhere on the board
/Radio_MCU/RFIO: C4.1, L2.1, U5.15 (RFIO)
/Radio_MCU/STATUS_LED: R9.1, U5.21 (PA9)
BTN: C5.1, R13.2, R15.2, U5.7 (PB4)
CS_EXT_3_OUT: U5.25 (PB9); also elsewhere on the board
E5_RX: J7.8, U5.18 (PA3)
E5_TX: J7.9, U5.19 (PA2)
GND: C4.2, C5.2, C10.2, C40.2, D3.1 (K), J1.2 (GND_1), J1.3 (GND_2), J1.4 (GND_3), J3.7, J3.8, J4.7, J4.8, J7.3, J7.5, R23.2, SW2.1, U5.2 (GND), U5.14 (GND), U5.16 (GND), U5.22 (GND); also elsewhere on the board
I2C_INT0: J3.6, U5.9 (PB7)
I2C_INT1: J4.6, U5.8 (PB3)
LED1: U5.10 (PB6); also elsewhere on the board
LED2: U5.11 (PB5); also elsewhere on the board
LED3: U5.12 (PC1); also elsewhere on the board
MCU_FAULT_N: U5.28 (PB0); also elsewhere on the board
MCU_SLEEP_N: U5.23 (PA0); also elsewhere on the board
MISO_EXT_3_OUT: U5.26 (PB14); also elsewhere on the board
MOSI_EXT_3_OUT: U5.27 (PA10); also elsewhere on the board
unnamed: D3.2 (A), R9.2
unnamed: C40.1, J1.1 (SIGNAL), L2.2
unnamed: R15.1, SW2.2
SCL: J3.5, J4.5, R10.2, U5.5 (PB15)
SCLK_EXT_3_OUT: U5.24 (PB13~); also elsewhere on the board
SDA: J3.3, J4.3, R6.2, U5.6 (PA15)
SWCLK: J7.4, U5.4 (PA14)
SWDIO: J7.2, U5.3 (PA13)
WIO_RESET: C25.2, J7.10, R23.1, U5.17 (RST)

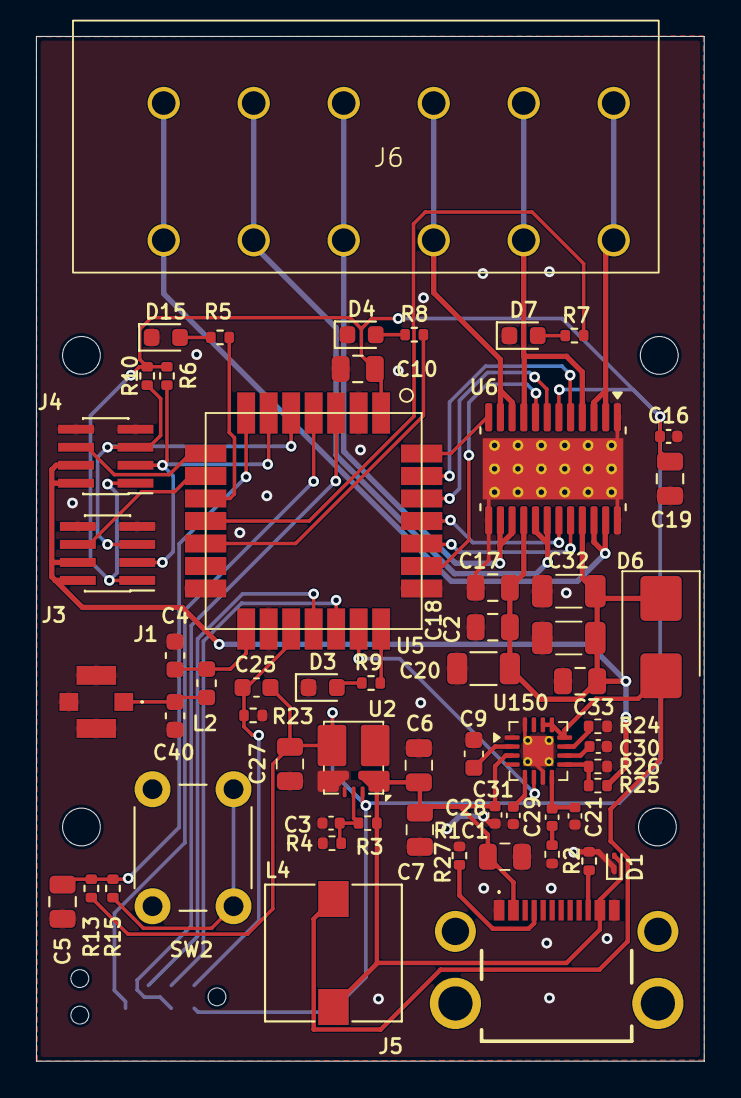
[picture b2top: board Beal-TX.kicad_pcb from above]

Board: 2 copper layers, 37.1 x 56.9 mm, 64 parts (1 on the bottom side), 49 nets.
